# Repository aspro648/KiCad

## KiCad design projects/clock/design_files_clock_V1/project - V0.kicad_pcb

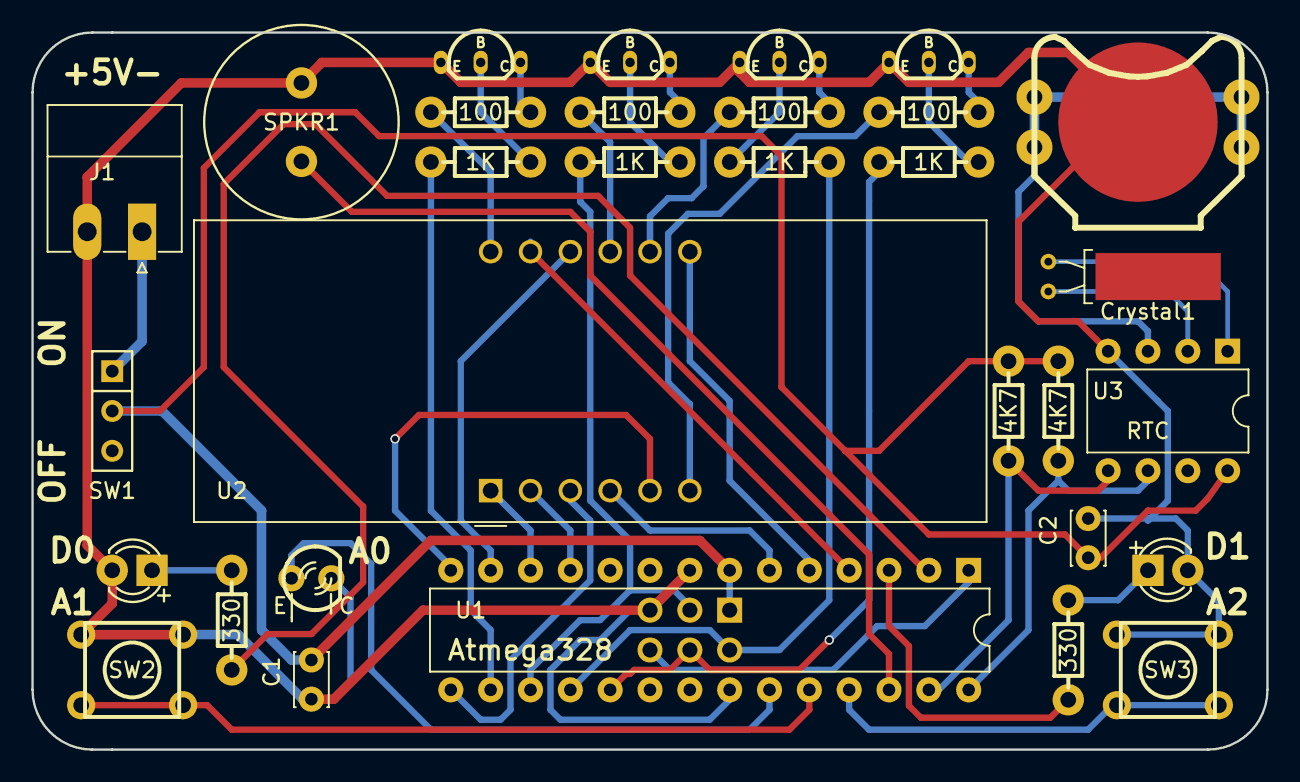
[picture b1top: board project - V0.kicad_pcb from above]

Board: 2 copper layers, 78.7 x 45.7 mm, 34 parts (1 on the bottom side), 41 nets.

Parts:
BT2: 3V; BATT_12mm_TH
C1, C2: 0.1uF; C_Disc_D3.4mm_W2.1mm_P2.50mm
CON1: ISP; AVR-ISP-6
Crystal1: 32.768; Crystal_C38-LF_d3.0mm_l8.0mm_Horizontal_1EP_style1
D1, D2: LED; LED-3MM
J1: PWR; PhoenixContact_MC-G_02x3.50mm_Angled
Q1: Photo; PHOTO_TRANS
Q2, Q3, Q4, Q5: 2N2222; TO-92_NPN_EBC_wide
R1, R2: 330; Resistor_Horz
R3, R4, R5, R6: 1K; Resistor_Horz
R7, R8, R9, R10: 100; Resistor_Horz
R11, R12: 4K7; Resistor_Horz
SPKR1: Speaker; PS1240_piezo
SW1: PWR; SW_Micro_SPST
SW2, SW3: SW_Push; SW_PUSH_SMALL
U1: ATMEGA328P-PU; DIP-28_W7.62mm
U2: CC56-12CGKWA; CA56-12CGKWA
U3: RTC; DIP-8_W7.62mm
VAL: MadeInOregonRev25
VAL#2: MB225rev

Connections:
/A0: Q1.1, U1.23
/A1: SW2.1, U1.24
/A2: SW3.1, U1.25
/A3: SPKR1.1, U1.26
/A4: R12.1, U1.27, U3.5
/A5: R11.1, U1.28, U3.6
/D0: R1.2, U1.2
/D1: R2.2, U1.3
/D2: U1.4, U2.11
/D3: U1.5, U2.7
/D4: U1.6, U2.4
/D5: U1.11, U2.2
/D6: U1.12, U2.1
/D7: U1.13, U2.10
/D8: U1.14, U2.5
/D9: U1.15, U2.3
/D10: R3.2, U1.16
/D11: CON1.4, R4.2, U1.17
/D12: CON1.1, R5.2, U1.18
/D13: CON1.3, R6.2, U1.19
GND: BT2.2, C1.2, C2.1, CON1.6, D1.1, D2.1, J1.2, Q1.2, Q2.1, Q3.1, Q4.1, Q5.1, SPKR1.2, SW2.2, SW3.2, U1.8, U1.22, U3.4
unnamed: BT2.1, U3.3
unnamed: CON1.5, U1.1
unnamed: Crystal1.1, U3.1
unnamed: Crystal1.2, U3.2
unnamed: D1.2, R1.1
unnamed: D2.2, R2.1
unnamed: J1.1, SW1.1
unnamed: Q2.2, R3.1
unnamed: Q2.3, R7.1
unnamed: Q3.2, R4.1
unnamed: Q3.3, R8.1
unnamed: Q4.2, R5.1
unnamed: Q4.3, R9.1
unnamed: Q5.2, R6.1
unnamed: Q5.3, R10.1
unnamed: R7.2, U2.12
unnamed: R8.2, U2.9
unnamed: R9.2, U2.8
unnamed: R10.2, U2.6
VCC: C1.1, C2.2, CON1.2, R11.2, R12.2, SW1.2, U1.7, U3.8

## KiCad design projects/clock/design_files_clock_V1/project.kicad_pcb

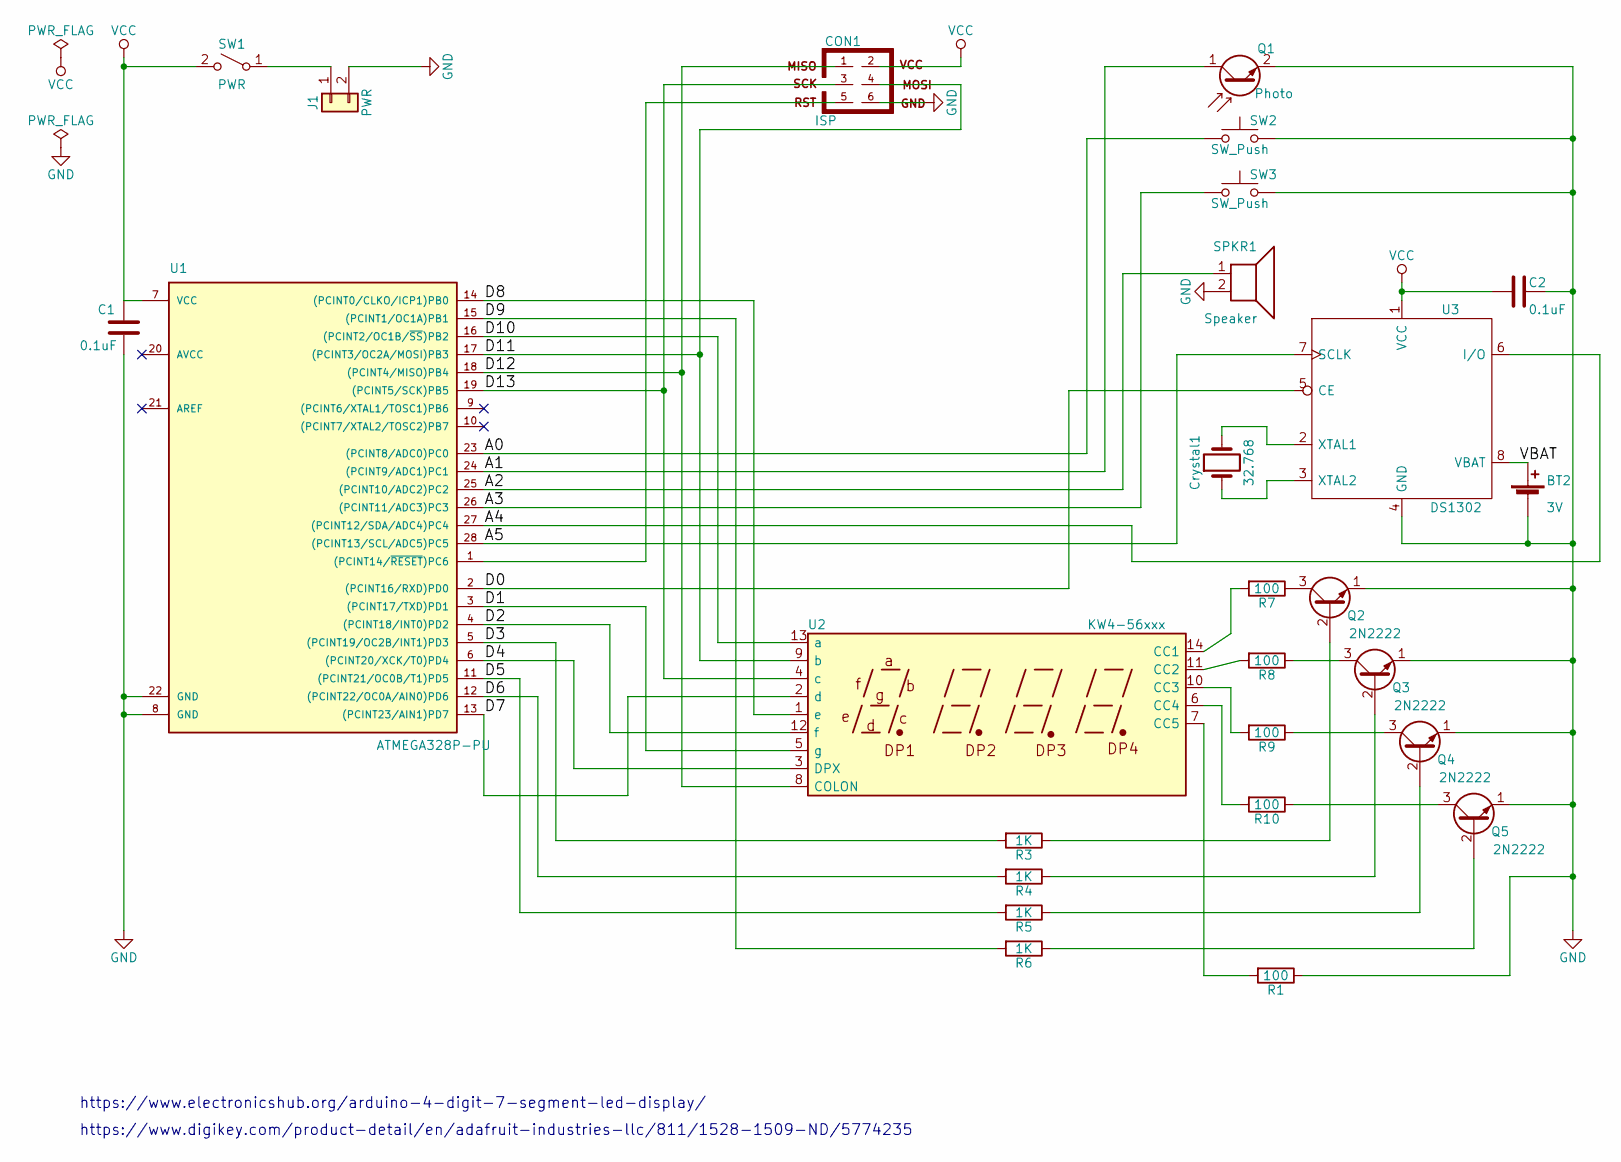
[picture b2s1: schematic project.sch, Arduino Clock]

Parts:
BT2: 3V; BATT_12mm_TH
C1, C2: 0.1uF; C_Disc_D3.4mm_W2.1mm_P2.50mm
CON1: ISP; AVR-ISP-6
Crystal1: 32.768; Crystal_C38-LF_d3.0mm_l8.0mm_Horizontal_1EP_style1
J1: PWR; PhoenixContact_MC-G_02x3.50mm_Angled
Q1: Photo; PHOTO_TRANS
Q2, Q3, Q4, Q5: 2N2222; TO-92_NPN_EBC_wide
R1, R7, R8, R9, R10: 100; Resistor_Horz
R3, R4, R5, R6: 1K; Resistor_Horz
SPKR1: Speaker; PS1240_piezo
SW1: PWR; SW_Micro_SPST
SW2, SW3: SW_Push; SW_PUSH_SMALL
U1: ATMEGA328P-PU; DIP-28_W7.62mm
U2: KW4-56xxx; CA56-12CGKWA
U3: DS1302; DIP-8_W7.62mm

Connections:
/A0: SW2.1, U1.23 ((PCINT8/ADC0)PC0)
/A1: Q1.1 (C), U1.24 ((PCINT9/ADC1)PC1)
/A2: SPKR1.1, U1.25 ((PCINT10/ADC2)PC2)
/A3: SW3.1, U1.26 ((PCINT11/ADC3)PC3)
/A4: U1.27 ((PCINT12/SDA/ADC4)PC4), U3.6 (I/O)
/A5: U1.28 ((PCINT13/SCL/ADC5)PC5), U3.7 (SCLK)
/D0: U1.2 ((PCINT16/RXD)PD0), U3.5 (CE)
/D1: U1.3 ((PCINT17/TXD)PD1), U2.5 (g)
/D2: U1.4 ((PCINT18/INT0)PD2), U2.12 (f)
/D3: R3.2, U1.5 ((PCINT19/OC2B/INT1)PD3)
/D4: U1.6 ((PCINT20/XCK/T0)PD4), U2.3 (DPX)
/D5: R5.2, U1.11 ((PCINT21/OC0B/T1)PD5)
/D6: R4.2, U1.12 ((PCINT22/OC0A/AIN0)PD6)
/D7: U1.13 ((PCINT23/AIN1)PD7), U2.2 (d)
/D8: U1.14 ((PCINT0/CLKO/ICP1)PB0), U2.1 (e)
/D9: R6.2, U1.15 ((PCINT1/OC1A)PB1)
/D10: U1.16 ((PCINT2/OC1B/~SS~)PB2), U2.13 (a)
/D11: CON1.4, U1.17 ((PCINT3/OC2A/MOSI)PB3), U2.9 (b)
/D12: CON1.1, U1.18 ((PCINT4/MISO)PB4), U2.8 (COLON)
/D13: CON1.3, U1.19 ((PCINT5/SCK)PB5), U2.4 (c)
/VBAT: BT2.1 (+), U3.8 (VBAT)
GND: BT2.2 (-), C1.2, C2.1, CON1.6, J1.2, Q1.2 (E), Q2.1 (E), Q3.1 (E), Q4.1 (E), Q5.1 (E), R1.1, SPKR1.2, SW2.2, SW3.2, U1.8 (GND), U1.22 (GND), U3.4 (GND)
unnamed: CON1.5, U1.1 ((PCINT14/~RESET~)PC6)
unnamed: Crystal1.1, U3.3 (XTAL2)
unnamed: Crystal1.2, U3.2 (XTAL1)
unnamed: J1.1, SW1.1 (A)
unnamed: Q2.2 (B), R3.1
unnamed: Q2.3 (C), R7.1
unnamed: Q3.2 (B), R4.1
unnamed: Q3.3 (C), R8.1
unnamed: Q4.2 (B), R5.1
unnamed: Q4.3 (C), R9.1
unnamed: Q5.2 (B), R6.1
unnamed: Q5.3 (C), R10.1
unnamed: R1.2, U2.7 (CC5)
unnamed: R7.2, U2.14 (CC1)
unnamed: R8.2, U2.11 (CC2)
unnamed: R9.2, U2.10 (CC3)
unnamed: R10.2, U2.6 (CC4)
VCC: C1.1, C2.2, CON1.2, SW1.2 (B), U1.7 (VCC), U3.1 (VCC)

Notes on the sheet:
https://www.electronicshub.org/arduino-4-digit-7-segment-led-display/
https://www.digikey.com/product-detail/en/adafruit-industries-llc/811/1528-1509-ND/5774235

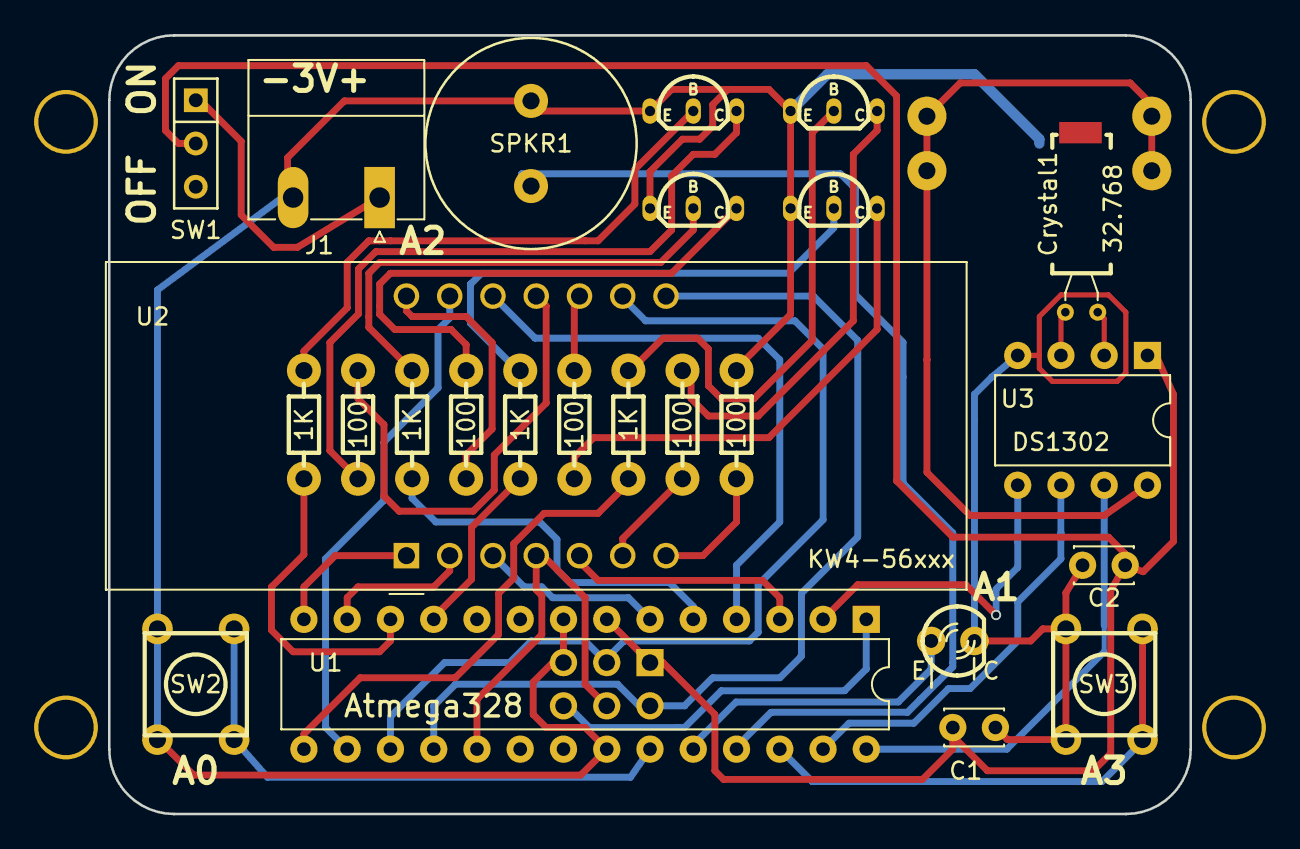
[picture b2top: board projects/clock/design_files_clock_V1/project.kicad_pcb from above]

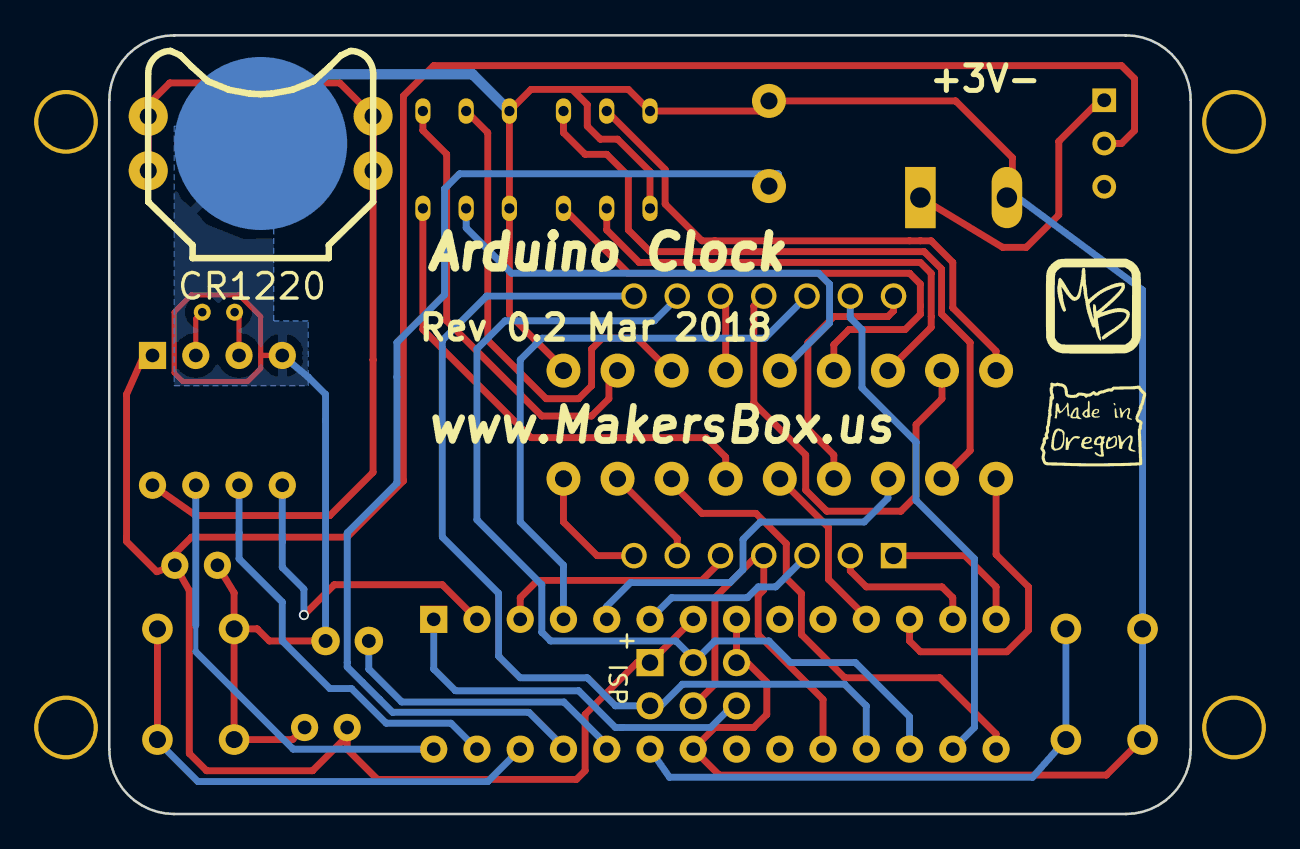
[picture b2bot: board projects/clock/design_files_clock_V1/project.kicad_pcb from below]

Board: 2 copper layers, 63.5 x 45.7 mm, 33 parts (2 on the bottom side), 40 nets.

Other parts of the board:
H1, H1#2, H1#3, H1#4: Hole; Pin_Header_Straight_1x01_Pitch2.54mm
VAL: MB225rev
VAL#2: MadeInOregonRev25

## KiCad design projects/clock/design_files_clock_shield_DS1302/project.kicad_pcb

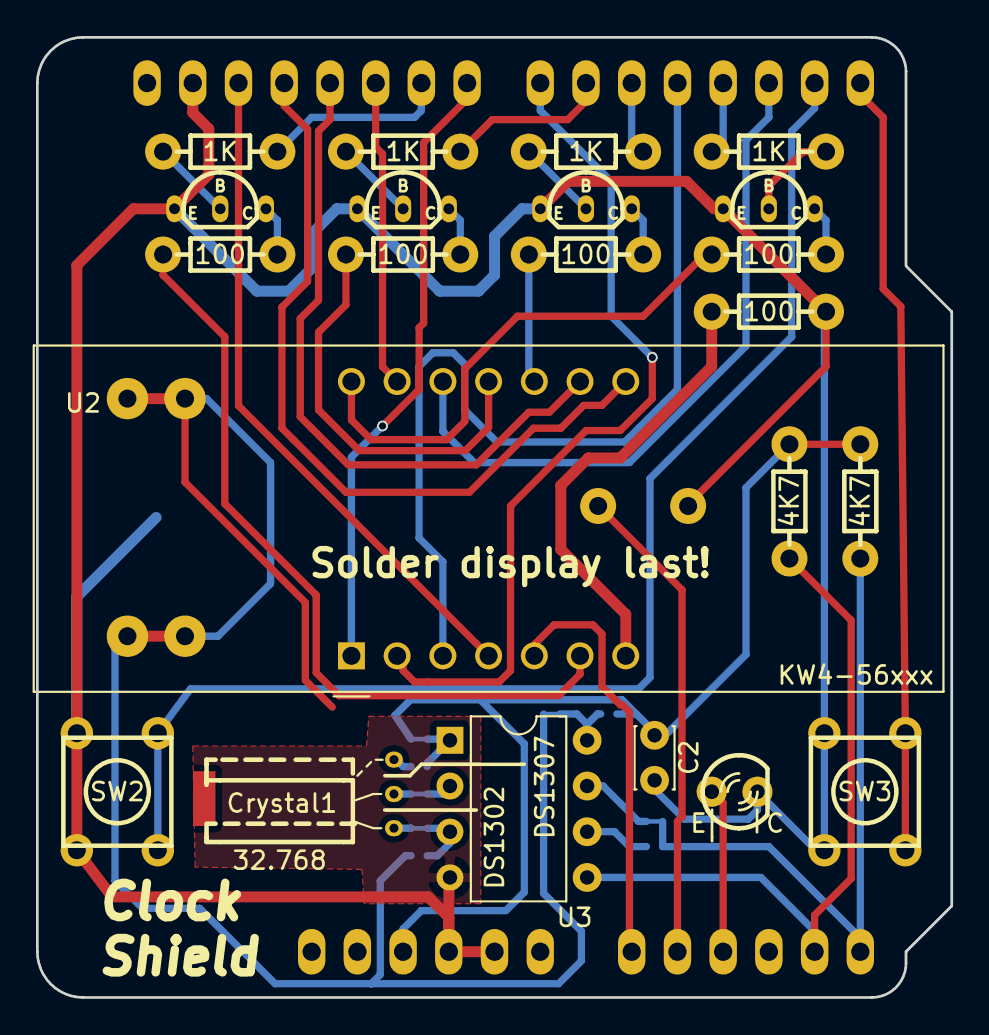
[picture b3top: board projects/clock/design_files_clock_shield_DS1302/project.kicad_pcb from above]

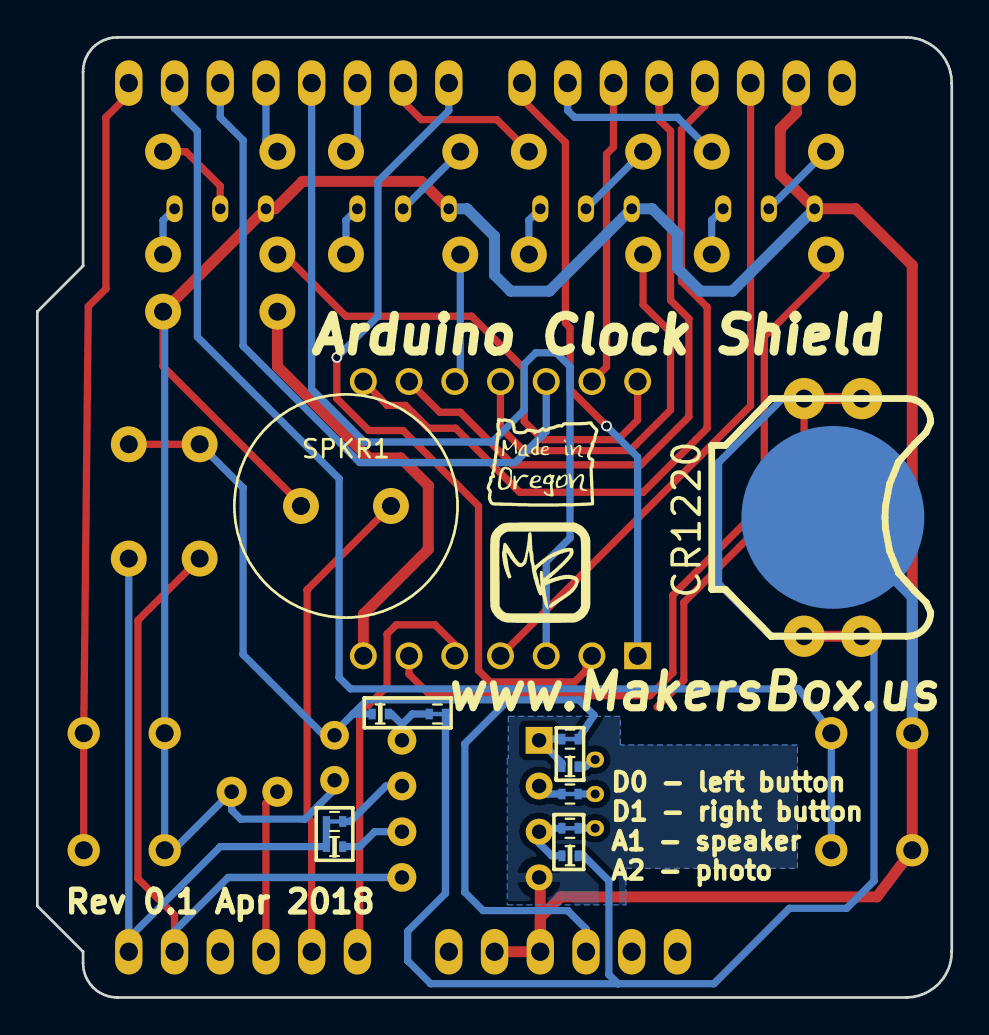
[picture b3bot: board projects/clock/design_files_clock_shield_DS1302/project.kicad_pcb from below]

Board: 2 copper layers, 50.8 x 53.3 mm, 36 parts (11 on the bottom side), 38 nets.

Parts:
BT2: 3V; BATT_12mm_TH
C2: 0.1uF; C_Disc_D3.4mm_W2.1mm_P2.50mm
Crystal1: 32.768; Crystal_C38-LF_d3.0mm_l8.0mm_Horizontal_1EP_style1
Q1: Photo; PHOTO_TRANS
Q2, Q3, Q4, Q5: 2N2222; TO-92_NPN_EBC_wide
R1, R7, R8, R9, R10: 100; Resistor_Horz
R2, R11, R12, R13, R19: 0; R_0402
R3, R4, R5, R6: 1K; Resistor_Horz
R14, R15, R16, R20: NC; R_0402
R17, R18: 4K7; Resistor_Horz
SHIELD1: ARDUINO_SHIELD
SPKR1: Speaker; PS1240_piezo
SW2, SW3: SW_Push; SW_PUSH_SMALL
U2: KW4-56xxx; CA56-12CGKWA
U3: DS1302; DIP-8_W7.62mm
VAL: MB225rev
VAL#2: MadeInOregonRev25

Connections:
/A0: SHIELD1.AD0, U2.5
/A1: SHIELD1.AD1, SPKR1.1
/A2: Q1.1, SHIELD1.AD2
/A4: R18.1, SHIELD1.AD4, U3.5
/A5: R17.1, R19.1, R19.2, R20.2, SHIELD1.AD5, U3.7
/D0: SHIELD1.0, SW3.1
/D1: SHIELD1.1, SW2.1
/D2: SHIELD1.2, U2.12
/D3: R3.2, SHIELD1.3
/D4: SHIELD1.4, U2.3
/D5: R5.2, SHIELD1.5
/D6: R4.2, SHIELD1.6
/D7: SHIELD1.7, U2.2
/D8: SHIELD1.8, U2.1
/D9: R6.2, SHIELD1.9
/D10: SHIELD1.10, U2.13
/D11: SHIELD1.11, U2.9
/D12: SHIELD1.12, U2.8
/D13: SHIELD1.13, U2.4
/VBAT: BT2.1, R13.1, R13.2, R14.2, R16.2, U3.8
GND: BT2.2, C2.1, Q1.2, Q2.1, Q3.1, Q4.1, Q5.1, R1.1, SHIELD1.GND1, SHIELD1.GND2, SHIELD1.GND3, SPKR1.2, SW2.2, SW3.2, U3.4
unnamed: Crystal1.1, R11.1, R11.2, R14.1, R15.2, U3.3
unnamed: Crystal1.2, R2.1, R2.2, U3.2
unnamed: Q2.2, R3.1
unnamed: Q2.3, R7.1
unnamed: Q3.2, R4.1
unnamed: Q3.3, R8.1
unnamed: Q4.2, R5.1
unnamed: Q4.3, R9.1
unnamed: Q5.2, R6.1
unnamed: Q5.3, R10.1
unnamed: R1.2, U2.7
unnamed: R7.2, U2.14
unnamed: R8.2, U2.11
unnamed: R9.2, U2.10
unnamed: R10.2, U2.6
unnamed: R20.1, U3.6
VCC: C2.2, R12.1, R12.2, R15.1, R16.1, R17.2, R18.2, SHIELD1.5V, U3.1

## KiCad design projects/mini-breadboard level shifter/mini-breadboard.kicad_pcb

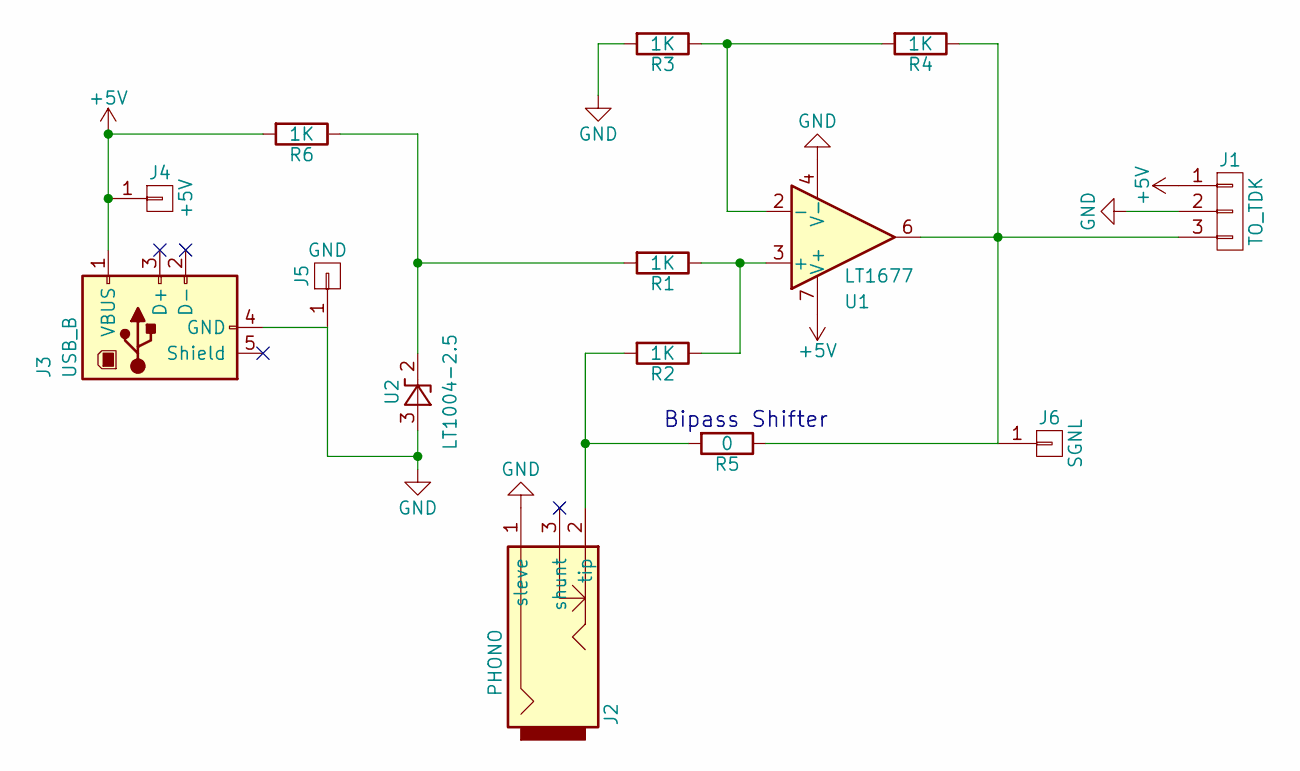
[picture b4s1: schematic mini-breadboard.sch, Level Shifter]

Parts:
J1: TO_TDK; Pin_Header_Straight_1x03_Pitch2.54mm
J2: PHONO; rca_yellow
J3: USB_B
J4: +5V; Pin_Header_Straight_1x01_Pitch1.27mm
J5: GND; Pin_Header_Straight_1x01_Pitch1.27mm
J6: SGNL; Pin_Header_Straight_1x01_Pitch1.27mm
R1, R2, R3, R4, R6: 1K; Resistor_Horz
R5: 0; R_0603
U1: LT1677; DIP-8_W7.62mm
U2: LT1004-2.5; TO-92_Inline_Narrow_Oval

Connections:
+5V: J1.1, J3.1 (VBUS), J4.1, R6.2, U1.7 (V+)
GND: J1.2, J2.1 (sleve), J3.4 (GND), J5.1, R3.2, U1.4 (V-), U2.3 (A)
unnamed: J1.3, J6.1, R4.1, R5.1, U1.6
unnamed: J2.2 (tip), R2.2, R5.2
unnamed: R1.1, R2.1, U1.3 (+)
unnamed: R1.2, R6.1, U2.2 (K)
unnamed: R3.1, R4.2, U1.2 (-)

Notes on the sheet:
Bipass Shifter

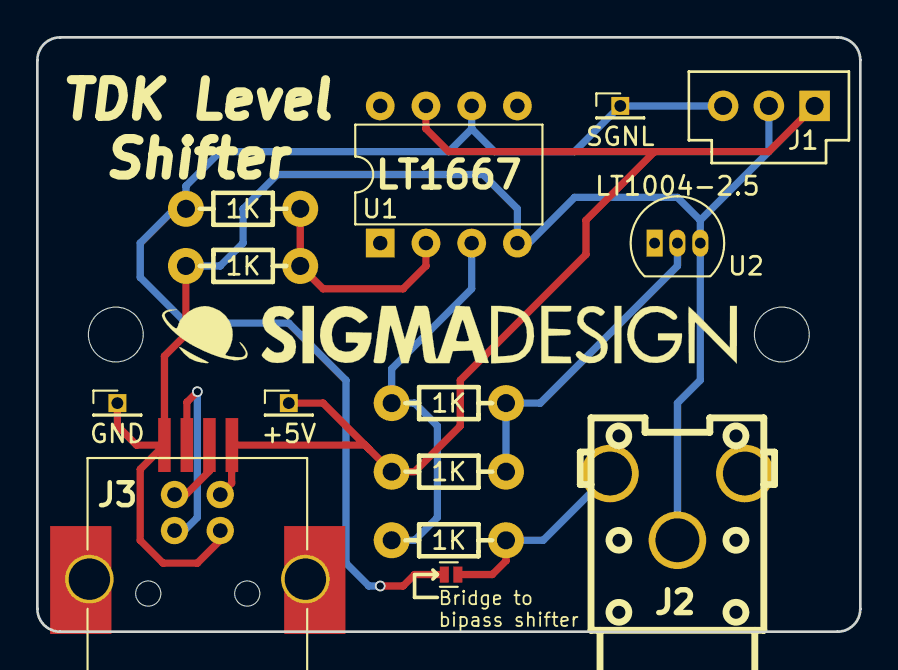
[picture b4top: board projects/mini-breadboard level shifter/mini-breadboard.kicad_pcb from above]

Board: 2 copper layers, 45.7 x 33.0 mm, 14 parts (0 on the bottom side), 7 nets.

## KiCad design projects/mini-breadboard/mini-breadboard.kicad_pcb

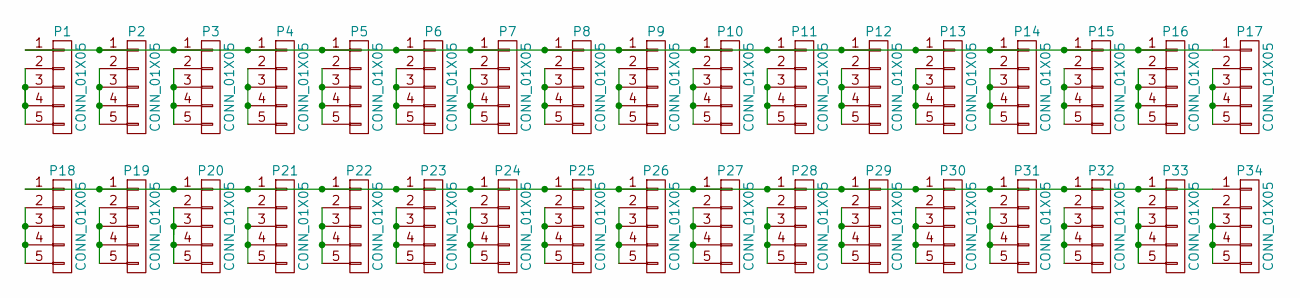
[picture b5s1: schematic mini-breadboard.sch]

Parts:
P1, P2, P3, P4, P5, P6, P7, P8, P9, P10, P11, P12, P13, P14, P15, P16, P17, P18, P19, P20, P21, P22, P23, P24, P25, P26, P27, P28, P29, P30, P31, P32, P33, P34: CONN_01X05; Pin_Header_Straight_1x05

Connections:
unnamed: P1.1, P2.1, P3.1, P4.1, P5.1, P6.1, P7.1, P8.1, P9.1, P10.1, P11.1, P12.1, P13.1, P14.1, P15.1, P16.1, P17.1
unnamed: P1.2, P1.3, P1.4, P1.5
unnamed: P2.2, P2.3, P2.4, P2.5
unnamed: P3.2, P3.3, P3.4, P3.5
unnamed: P4.2, P4.3, P4.4, P4.5
unnamed: P5.2, P5.3, P5.4, P5.5
unnamed: P6.2, P6.3, P6.4, P6.5
unnamed: P7.2, P7.3, P7.4, P7.5
unnamed: P8.2, P8.3, P8.4, P8.5
unnamed: P9.2, P9.3, P9.4, P9.5
unnamed: P10.2, P10.3, P10.4, P10.5
unnamed: P11.2, P11.3, P11.4, P11.5
unnamed: P12.2, P12.3, P12.4, P12.5
unnamed: P13.2, P13.3, P13.4, P13.5
unnamed: P14.2, P14.3, P14.4, P14.5
unnamed: P15.2, P15.3, P15.4, P15.5
unnamed: P16.2, P16.3, P16.4, P16.5
unnamed: P17.2, P17.3, P17.4, P17.5
unnamed: P18.1, P19.1, P20.1, P21.1, P22.1, P23.1, P24.1, P25.1, P26.1, P27.1, P28.1, P29.1, P30.1, P31.1, P32.1, P33.1, P34.1
unnamed: P18.2, P18.3, P18.4, P18.5
unnamed: P19.2, P19.3, P19.4, P19.5
unnamed: P20.2, P20.3, P20.4, P20.5
unnamed: P21.2, P21.3, P21.4, P21.5
unnamed: P22.2, P22.3, P22.4, P22.5
unnamed: P23.2, P23.3, P23.4, P23.5
unnamed: P24.2, P24.3, P24.4, P24.5
unnamed: P25.2, P25.3, P25.4, P25.5
unnamed: P26.2, P26.3, P26.4, P26.5
unnamed: P27.2, P27.3, P27.4, P27.5
unnamed: P28.2, P28.3, P28.4, P28.5
unnamed: P29.2, P29.3, P29.4, P29.5
unnamed: P30.2, P30.3, P30.4, P30.5
unnamed: P31.2, P31.3, P31.4, P31.5
unnamed: P32.2, P32.3, P32.4, P32.5
unnamed: P33.2, P33.3, P33.4, P33.5
unnamed: P34.2, P34.3, P34.4, P34.5

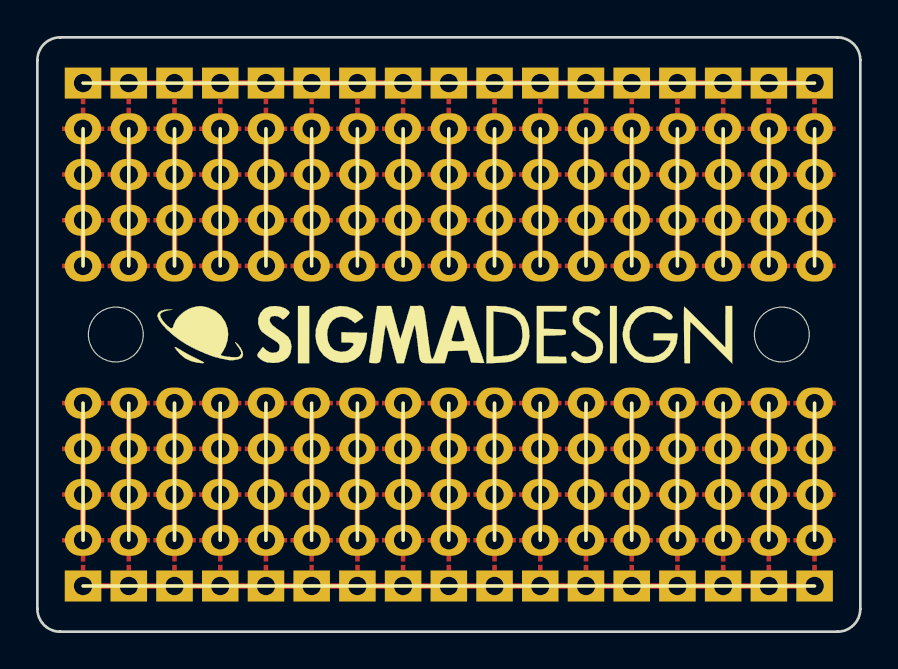
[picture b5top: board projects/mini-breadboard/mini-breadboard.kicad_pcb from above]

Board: 2 copper layers, 45.7 x 33.0 mm, 34 parts (0 on the bottom side), 36 nets.

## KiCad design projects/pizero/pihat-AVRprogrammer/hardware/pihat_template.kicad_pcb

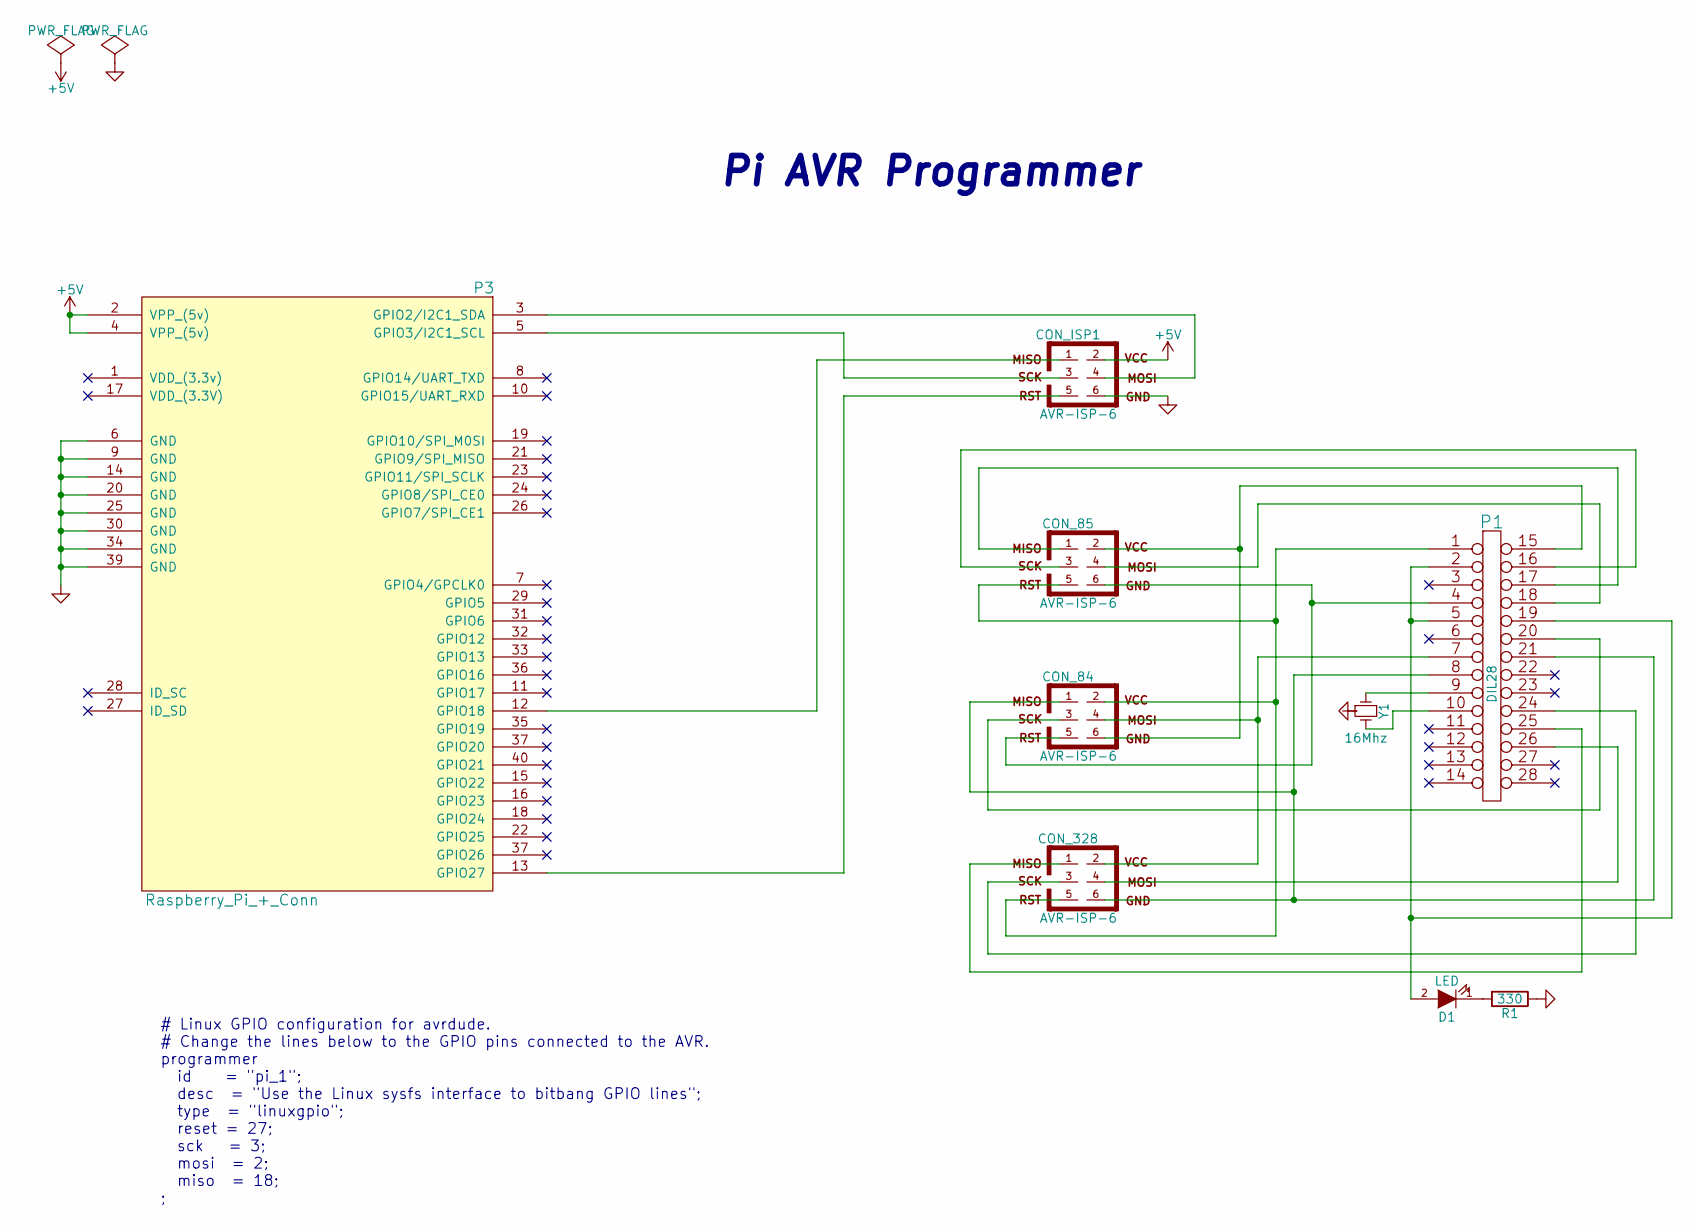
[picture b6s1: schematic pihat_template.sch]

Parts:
CON_84, CON_85, CON_328: AVR-ISP-6
CON_ISP1: AVR-ISP-6
D1: LED; LED-3MM
P1: DIL28; Zif_228-3341
P3: Raspberry_Pi_+_Conn; vasch_strip_20x2; Mouser Part No. 517-30340-6002
R1: 330; Resistor_Horz
Y1: 16Mhz; Crystal_HC49-U_Vertical_3Pin

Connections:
+5V: CON_ISP1.2, P3.2 (VPP_(5v)), P3.4 (VPP_(5v))
GND: CON_ISP1.6, P3.6 (GND), P3.9 (GND), P3.14 (GND), P3.20 (GND), P3.25 (GND), P3.30 (GND), P3.34 (GND), P3.39 (GND), R1.1, Y1.3 (GND)
unnamed: CON_84.3, P1.20
unnamed: CON_84.5, CON_85.6, P1.4
unnamed: CON_84.6, CON_85.2, P1.15
unnamed: CON_85.1, P1.17
unnamed: CON_85.3, P1.16
unnamed: CON_85.4, P1.18
unnamed: CON_328.1, P1.25
unnamed: CON_84.4, CON_328.2, P1.7
unnamed: CON_328.3, P1.24
unnamed: CON_328.4, P1.26
unnamed: CON_84.2, CON_85.5, CON_328.5, P1.1
unnamed: CON_84.1, CON_328.6, P1.8, P1.21
unnamed: CON_ISP1.1, P3.12 (GPIO18)
unnamed: CON_ISP1.3, P3.5 (GPIO3/I2C1_SCL)
unnamed: CON_ISP1.4, P3.3 (GPIO2/I2C1_SDA)
unnamed: CON_ISP1.5, P3.13 (GPIO27)
unnamed: D1.1 (K), R1.2
unnamed: D1.2 (A), P1.2, P1.5, P1.19
unnamed: P1.9, Y1.1
unnamed: P1.10, Y1.2

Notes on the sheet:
Pi AVR Programmer
# Linux GPIO configuration for avrdude. # Change the lines below to the GPIO pins connected to the AVR. programmer id = "pi_1"; desc = "Use the Linux sysfs interface to bitbang GPIO lines"; type = "linuxgpio"; reset = 27; sck = 3; mosi = 2; miso = 18; ;

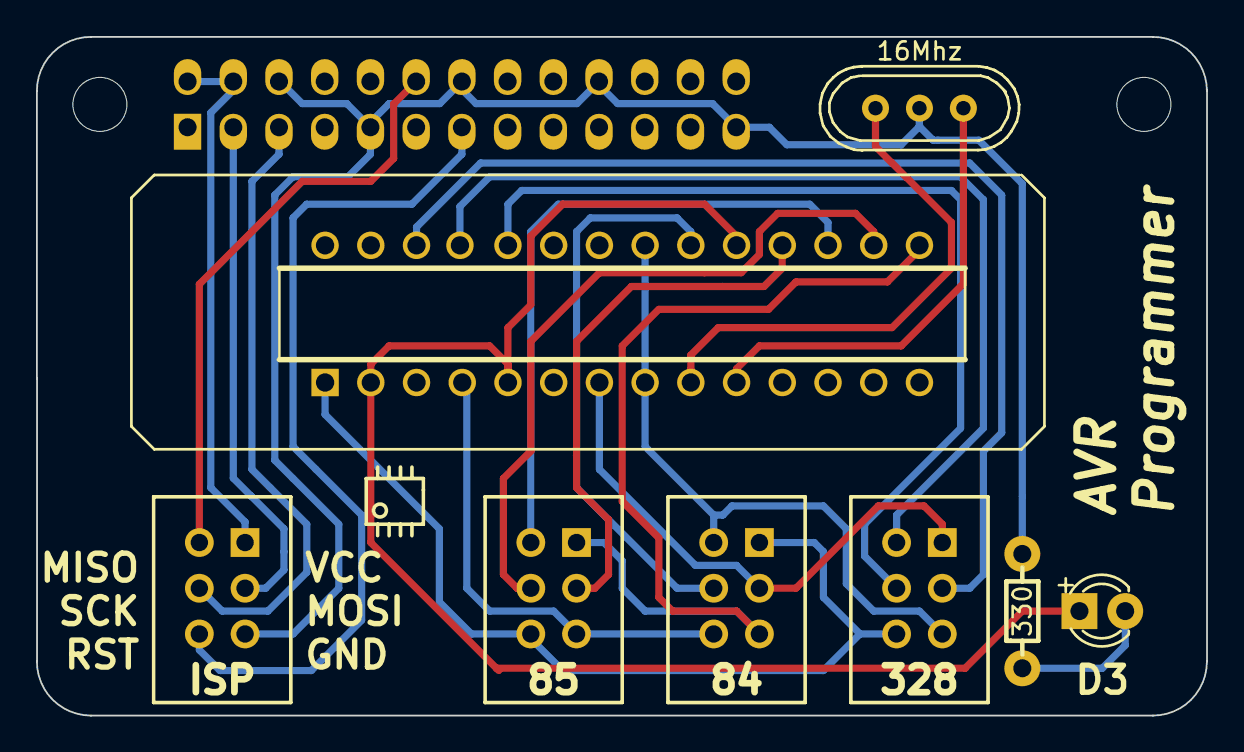
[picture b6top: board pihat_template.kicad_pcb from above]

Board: 2 copper layers, 65.0 x 37.7 mm, 11 parts (0 on the bottom side), 22 nets.

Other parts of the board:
VAL: MadeInOregonRev25
VAL#2: MB225rev

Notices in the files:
projects/pizero/pihat-AVRprogrammer/hardware/pihat_template.kicad_pcb:
License: CERN OHL V1.2
